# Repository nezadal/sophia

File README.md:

# Sophia
Bee Hive Scale with GSM data tranfer to ThingSpeak server, runs on battery with solar panel charging. Bee Hive Scale monitors bee hive weight, temperature, humidity and voltage of battery. These values are measured hourly, trasfered and stored to ThingSpeak server. 

Hardware:

- Arduino Pro Mini, 3,3V,
- 4x loadcell, a 50kg,
- HX711 amplifier,
- 2x 18650 3,7 V Lion cell,
- DHT 22 humidity and temperature sensor,
- MT3608 step-up,
- IRL 540 NPBF transistor,
- SIM800L GSM modul,
- Solar panel 6V, 4,5W,
- Solar charger module CN 3791, 6V, 
- some resistors, capacitators, wiring, switch...

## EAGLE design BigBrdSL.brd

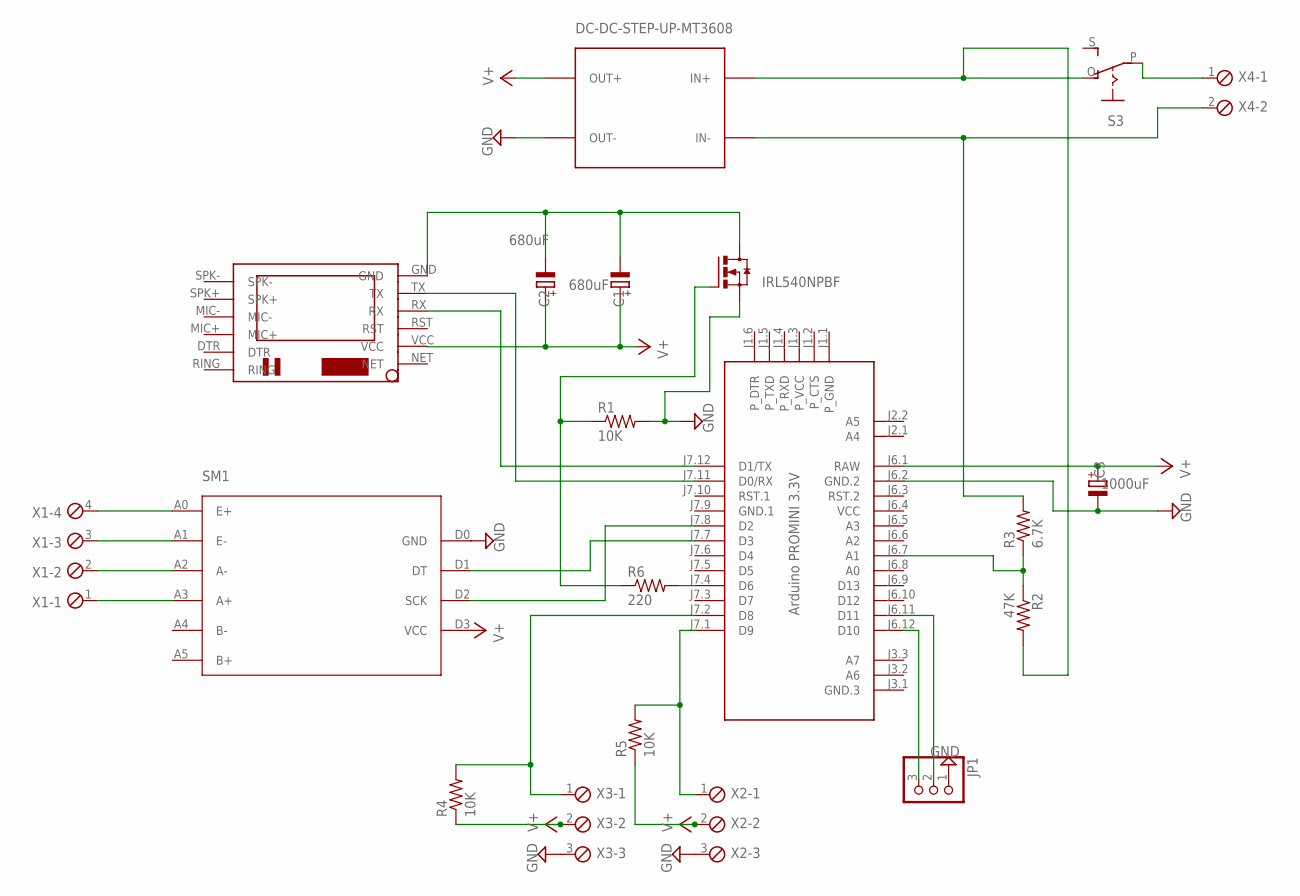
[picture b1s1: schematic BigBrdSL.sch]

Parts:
C1, C2: 680uF; E3,5-8
C3: 1000uF; E3,5-8
IRL540NPBF: IRF520NPBF; TO-220; MPN IRL540NPBF; DIGIKEY_PART_NUMBER IRlL540NPBF
JP1: PINHD-1X3; 1X03
M1: ARDUINO-PRO-MINI-5.0V; ARDUINO-PRO-MINI
MT36-08: DC-DC-STEP-UP-MT3608
R1, R4, R5: 10K; 0207/7
R2: 47K; 0207/7
R3: 6.7K; 0207/7
R6: 220; 0207/7
S3: EG1218S; EG1218
SM1: HX711
U$3: SIM800LMODULE
X1: MPT4; 4POL254
X2, X3: MPT3; 3POL254
X4: MPT2; 2POL254

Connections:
GND: C3.-, IRL540NPBF.S, JP1.1, M1.J6.2 (GND.2), MT36-08.OUT-, R1.2, SM1.D0 (GND), X2.3, X3.3
GND.1: M1.J7.9 (GND.1)
unnamed: M1.J7.1 (D9), R5.2, X2.1
unnamed: MT36-08.IN+, R2.2, S3.O
unnamed: IRL540NPBF.G, R1.1, R6.1
unnamed: M1.J7.11 (D0/RX), U$3.TX
unnamed: M1.J7.7 (D3), SM1.D1 (DT)
unnamed: M1.J7.12 (D1/TX), U$3.RX
unnamed: M1.J7.8 (D2), SM1.D2 (SCK)
unnamed: JP1.3, M1.J6.12 (D10)
unnamed: M1.J7.4 (D6), R6.2
unnamed: MT36-08.IN-, R3.2, X4.2
unnamed: M1.J6.7 (A1), R2.1, R3.1
unnamed: C1.-, C2.-, IRL540NPBF.D, U$3.GND
unnamed: JP1.2, M1.J6.11 (D11)
unnamed: SM1.A0 (E+), X1.4
unnamed: SM1.A1 (E-), X1.3
unnamed: SM1.A2 (A-), X1.2
unnamed: SM1.A3 (A+), X1.1
unnamed: S3.P, X4.1
unnamed: M1.J7.2 (D8), R4.2, X3.1
V+: C1.+, C2.+, C3.+, M1.J6.1 (RAW), MT36-08.OUT+, R4.1, R5.1, SM1.D3 (VCC), U$3.VCC, X2.2, X3.2
VCC: M1.J6.4 (VCC)

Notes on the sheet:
Arduino PROMINI 3.3V

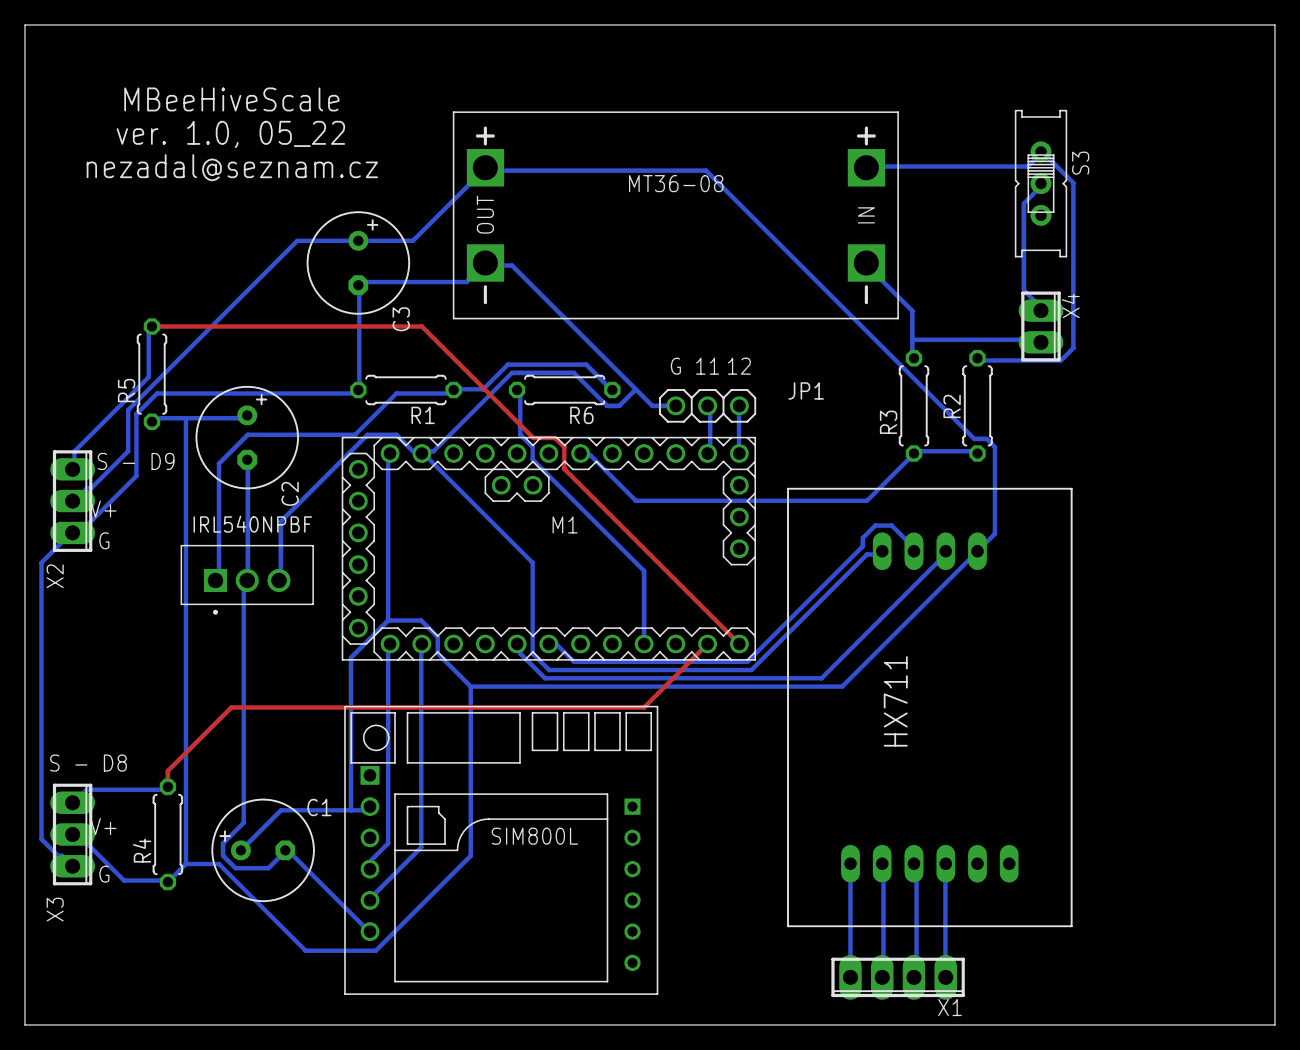
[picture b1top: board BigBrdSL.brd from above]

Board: 2 copper layers, 100.0 x 80.0 mm, 20 parts (0 on the bottom side), 21 nets.

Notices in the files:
parts and their libraries:
diy-modules: Released under the Creative Commons Attribution 4.0 International License: http://creativecommons.org/licenses/by/4.0
